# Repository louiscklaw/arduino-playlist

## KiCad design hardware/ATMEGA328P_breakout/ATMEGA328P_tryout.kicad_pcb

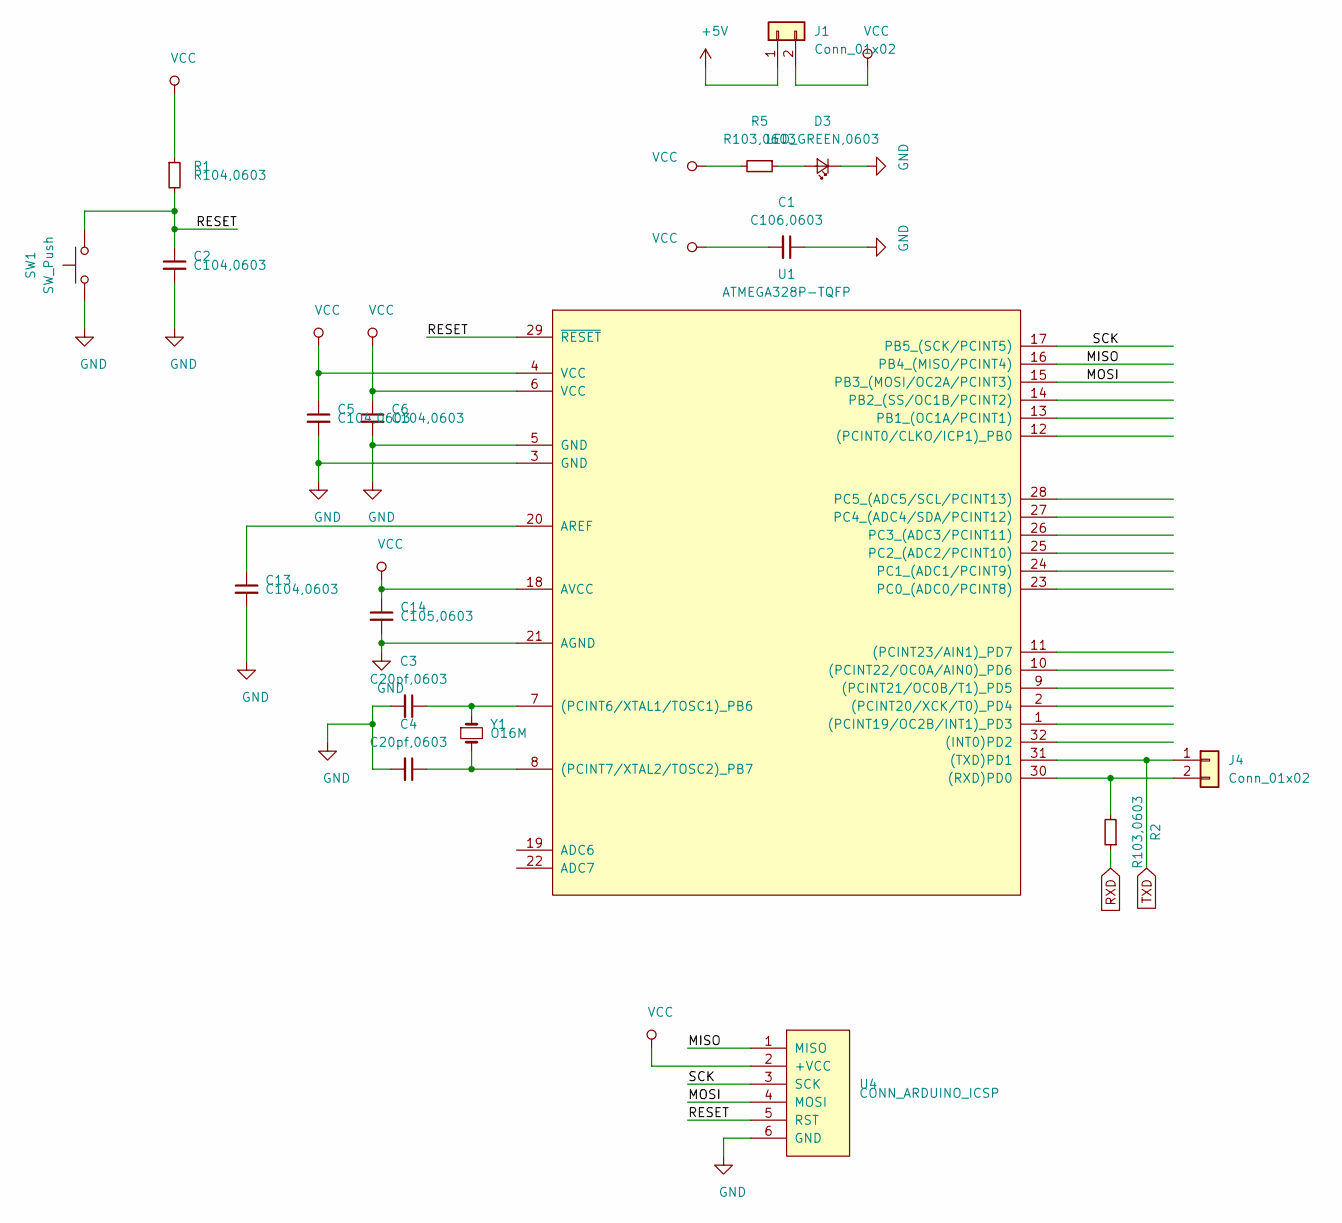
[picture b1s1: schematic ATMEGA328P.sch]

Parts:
C1: C106,0603; C_0603_1608Metric_Pad1.05x0.95mm_HandSolder
C2, C5, C6, C13: C104,0603; C_0603_1608Metric_Pad1.05x0.95mm_HandSolder
C3, C4: C20pf,0603; C_0603_1608Metric_Pad1.05x0.95mm_HandSolder
C14: C105,0603; C_0603_1608Metric_Pad1.05x0.95mm_HandSolder
D3: LED_GREEN,0603; LED_0603_1608Metric_Pad1.05x0.95mm_HandSolder
J1: Conn_01x02; PinHeader_1x02_P1.27mm_Vertical
J4: Conn_01x02; PinHeader_1x02_P2.54mm_Vertical
R1: R104,0603; R_0603_1608Metric_Pad1.05x0.95mm_HandSolder
R2, R5: R103,0603; R_0603_1608Metric_Pad1.05x0.95mm_HandSolder
SW1: SW_Push; SW_SPST_CK_RS282G05A3
U1: ATMEGA328P-TQFP; TQFP-32_7x7mm_P0.8mm
U4: CONN_ARDUINO_ICSP; PinHeader_2x03_P2.54mm_Vertical
Y1: O16M; Crystal_SMD_HC49-SD

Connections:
+5V: J1.1
/ATMEGA328P/MISO: U1.16 (PB4_(MISO/PCINT4)), U4.1 (MISO)
/ATMEGA328P/MOSI: U1.15 (PB3_(MOSI/OC2A/PCINT3)), U4.4 (MOSI)
/ATMEGA328P/RESET: C2.1, R1.2, SW1.2, U1.29 (~RESET~), U4.5 (RST)
/ATMEGA328P/SCK: U1.17 (PB5_(SCK/PCINT5)), U4.3 (SCK)
GND: C1.1, C2.2, C3.2, C4.2, C5.2, C6.2, C13.2, C14.2, D3.1 (K), SW1.1, U1.3 (GND), U1.5 (GND), U1.21 (AGND), U4.6 (GND)
unnamed: C3.1, U1.7 ((PCINT6/XTAL1/TOSC1)_PB6), Y1.1
unnamed: C4.1, U1.8 ((PCINT7/XTAL2/TOSC2)_PB7), Y1.2
unnamed: C13.1, U1.20 (AREF)
unnamed: D3.2 (A), R5.1
unnamed: J4.2, R2.2, U1.30 ((RXD)PD0)
RXD: R2.1
TXD: J4.1, U1.31 ((TXD)PD1)
VCC: C1.2, C5.1, C6.1, C14.1, J1.2, R1.1, R5.2, U1.4 (VCC), U1.6 (VCC), U1.18 (AVCC), U4.2 (+VCC)

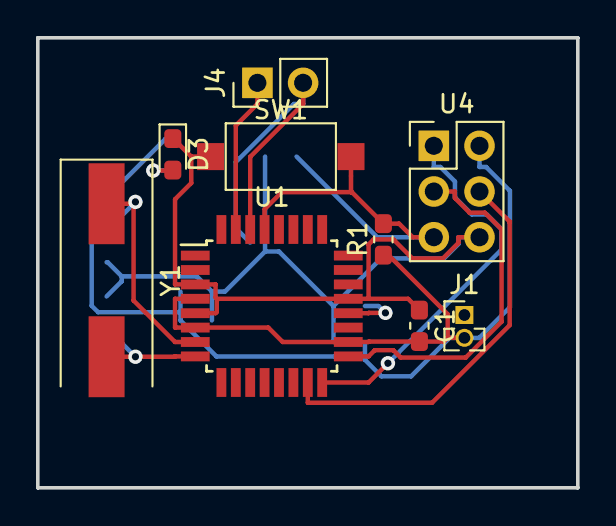
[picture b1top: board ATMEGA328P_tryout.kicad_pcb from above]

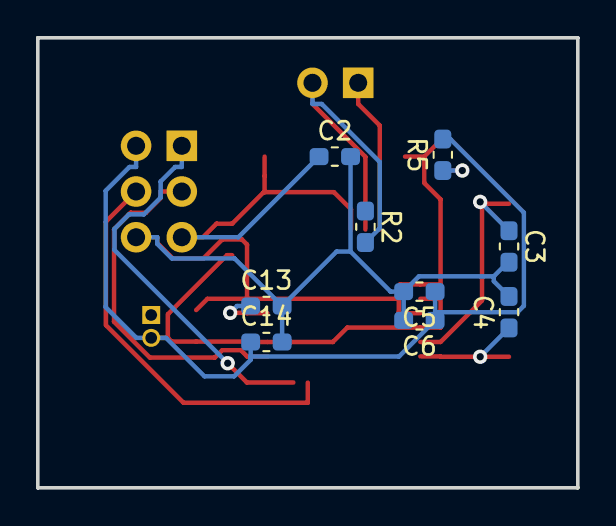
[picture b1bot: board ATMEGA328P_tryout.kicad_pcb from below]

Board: 2 copper layers, 30.0 x 25.0 mm, 18 parts (9 on the bottom side), 12 nets.

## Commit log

2020-07-23 update travis merger,
2020-07-23 update,
2020-07-23 updaste to add adafruit directory,
2020-08-08 adding merger files,
2020-09-27 init commit for github merger,
2020-09-27 update and test,
2020-10-27 Bump cryptography from 2.9.2 to 3.2 in /github-build-merger
    Bumps [cryptography](https://github.com/pyca/cryptography) from 2.9.2 to 3.2.
    - [Release notes](https://github.com/pyca/cryptography/releases)
    - [Changelog](https://github.com/pyca/cryptography/blob/master/CHANGELOG.rst)
    - [Commits](https://github.com/pyca/cryptography/compare/2.9.2...3.2)
2020-11-15 update scripts,
2021-02-26 Bump aiohttp from 3.6.2 to 3.7.4 in /github-build-merger
    Bumps [aiohttp](https://github.com/aio-libs/aiohttp) from 3.6.2 to 3.7.4.
    - [Release notes](https://github.com/aio-libs/aiohttp/releases)
    - [Changelog](https://github.com/aio-libs/aiohttp/blob/master/CHANGES.rst)
    - [Commits](https://github.com/aio-libs/aiohttp/compare/v3.6.2...v3.7.4)
2022-02-14 init commit,
